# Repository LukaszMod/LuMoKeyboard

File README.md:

# LuMoKeyboard
Is is repository for LuMo keyboard in version 0.1

The splitted keyboard has 64 keys. I needed keyboard with all alphanum chars (36) + special chars(11) + duplicated functions keys like 2x space, 2x return, r/l alt, r/l ctrl r/l shift and rest. It is designed with Keith Choc keys to be as thin as possible. Communication is done by ProMicro controller using Bluetooth, so no cable is needed* . Additional feature is power sharing that allows to join and charge both parts in the same time and borrow powers from one part to the second one. Keyboard can work with 5 devices. Current configuration does not support display because of usage ProMicro instead of Nice!Nano.

\* For charging only

# Parts

List of components needed to build both halves of the keyboard.  
PCBs were ordered from **JLCPCB**, keyboard parts from **AliExpress**, and bolts/spacers from **TME.eu**.

---

## Component List

| Component                  | Quantity | Notes                                                    | Links
|----------------------------|----------|----------------------------------------------------------|-----------------------------------------------------
| PCB main                   | 2 files  | Gerber files in repository                               |
| PCB top                    | 2 files  | Gerber files in repository                               |
| PCB bottom                 | 2 files  | Gerber files in repository                               |
| Microcontroller            | 2        | Pro Micro NRF52840                                       | [link](https://pl.aliexpress.com/item/1005006271881076.html)
| On-Off switch              | 2        | SS12D10                                                  | [link](https://pl.aliexpress.com/item/1005005633418066.html)
| Tactile switch             | 2        | Push Button 6×6×4.3 mm DIP                               | [link](https://pl.aliexpress.com/item/1005005917191424.html)
| Diodes                     | 64       | 1N4148 (SMD SOD-123 used, standard is also possible)     | [link](https://pl.aliexpress.com/item/1005005707644429.html)
| Magnetic connector         | 1 set    | Magnetic Pogo Pin Connector 2 Positions MG02254B angled  | [link](https://pl.aliexpress.com/item/1005005687037973.html)
| Batteries                  | 2        | 301230 3.7V 120mAh with JST 1.25 connector + PCM         | [link](https://pl.aliexpress.com/item/4000174240984.html)
| Connectors                 | 2        | JST 1.25 2Pin Straight needle                            | [link](https://pl.aliexpress.com/item/1005009890700220.html)
| Sockets                    | 64       | Kailh Hot-Swappable PCB Socket for low profile switches  | [link](https://pl.aliexpress.com/item/1005003873653184.html)
| Switches                   | 64       | Kailh Low Profile Choc Switch V1 1350                    | [link](https://pl.aliexpress.com/item/1005008806799106.html)
| Keycaps                    | 64       | Low Profile Choc PBT Keycaps for Kailh 1350 Choc         | [link](https://pl.aliexpress.com/item/1005006734545486.html)
| Bolts                      | 4        | Screw M2×4; 0.4; cheese head; Phillips PH1               | [link](https://www.tme.eu/pl/details/m2x4_d7985/sruby/kraftberg/)
| Spacers                    | 4        | Screwed spacer sleeve; 5mm length; M2 thread; hexagonal  | [link](https://www.tme.eu/pl/en/details/tff-m2x5_dr111/metal-spacers/dremec/111x05/)
| Rubber feet                | 4        | 3mm thick                                                |
| Polymer clay plastic mass  | small bag| Borrowed from kids 😅                                    | [link](https://pl.aliexpress.com/item/1005010076052629.html)

---

## BOM Table (2025 Prices)

| Item                                      | Quantity | Price (USD)        |
|-------------------------------------------|----------|--------------------|
| PCBs (3 × 5, incl. duties/taxes/shipping) | –        | $57.85             |
| Pro Micro NRF52840                        | 2        | $3.84              |
| SS12D00 On-Off Mini Slide Switch 3pin     | 20       | $1.05              |
| Tactile Push Button Switches              | 50       | $1.41              |
| SMD SOD-123 diode 1N4148                  | 100      | $1.25              |
| Magnetic Pogo Pin Connector (2 pos.)      | 1 set    | $1.78              |
| 301030 3.7V 120mAh battery                | 2        | $4.54              |
| JST 1.25 connectors                       | 10       | $1.25              |
| Kailh Hot-Swappable PCB Socket            | 100      | $13.39             |
| Kailh Low Profile Choc Switch V1 1350     | 70       | $26.28             |
| Keycaps                                   | 70       | $41.89             |
| Screwed spacer                            | 10       | $3.90              |
| Bolts                                     | 100      | $1.80              |
| Rubber Feet                               | 100      | $1.66              |
| Polymer clay plastic mass                 | –        | ?? (borrowed)      |

**Total cost: $161.89 + guilt** 😅  

---

# Tools Needed

Tweezers, soldering iron, solder paste, solder wire, cutters, isopropyl alcohol, screwdriver.

---

# Soldering

The first components to solder are the diodes. Diodes can be SMD or through-hole. For through-hole diodes, solder from the same side as the component (bottom side). The top side of the PCB should remain flat, without any leads. For SMD diodes, this issue does not exist. Diodes must be soldered according to the orientation &#x1CC0F;. The vertical line is also marked on the diode itself. 

To solder SMD components, first apply a small amount of solder paste to one pad, then place a drop of molten solder on the pad. Hold the SMD component with tweezers, reheat the solder, and attach one lead. Once it solidifies, solder the second lead.

Next, solder the sockets on the main PCB. Before soldering, press the switches into the top plate. Then join the top and main PCBs, and press the sockets from below. These two plates will not be separated again. After soldering, check all connections with a multimeter.

The next components to solder are the microcontroller, switches, JST connectors, and magnetic connectors. Ensure there is enough space between the microcontroller and PCB for the battery. On my PCB, I used a different JST connector, so I had to secure it with hot glue.

Finally, assemble the plates. First, screw the bolts through the top and middle plates into the spacers. Then attach the bottom plate and fasten it with the remaining bolts. Press foam clay into the space between the PCB plates. To smooth the surface of the joint, use a wet finger.

# Flash

## Installation of zmk 

The installation are provide on the webside:

[Installation zmk](https://zmk.dev/docs/user-setup#prerequisites)

Do not execute next sestion- 'Config Repo Setup'. 
After that copy folder `lumo` located in `zmk` from current repository into
`zmk/app/boards/shields`. Next open startscript.sh and set path to python virtual environment (line source /path_to_venv/bin/activate). At the end execute the file. 

Connect the left part of keyboard by USB to PC. Click twice reset button on the keyboard - MCU will be set in boot mode and you shall see new mounted device. Copy file `zmk/app/build/lumo_left/zephyr/zmk.uf2` into the device. Do the same steps for right part.

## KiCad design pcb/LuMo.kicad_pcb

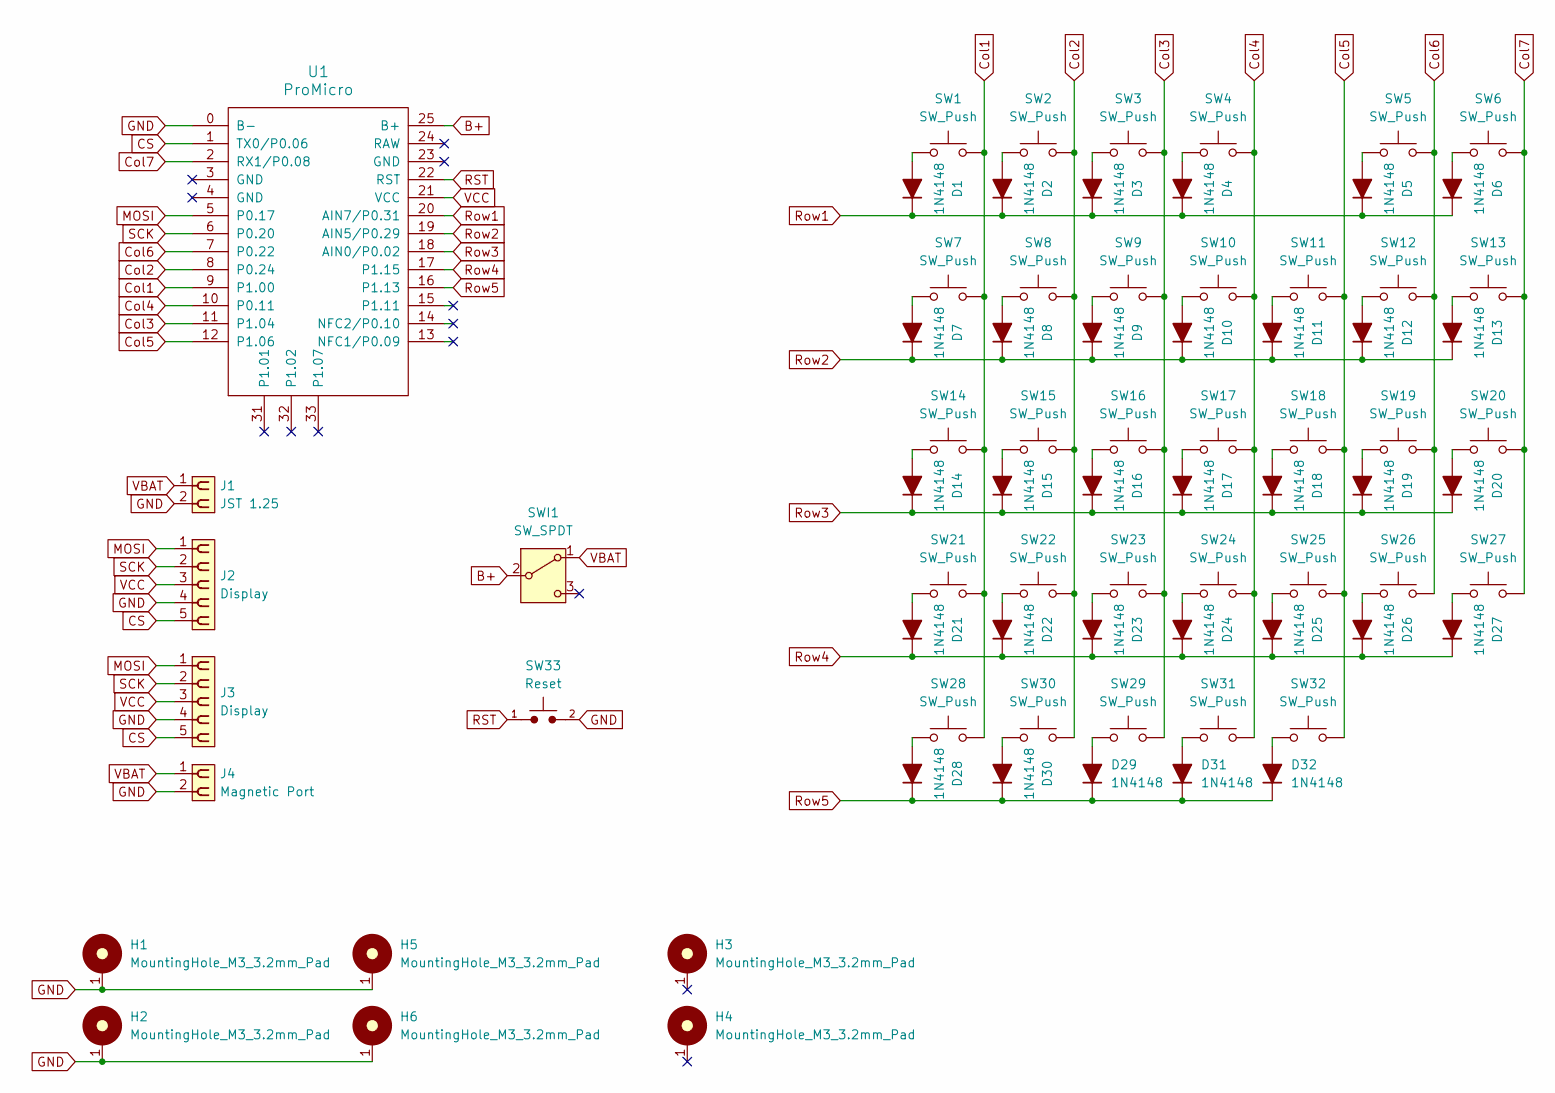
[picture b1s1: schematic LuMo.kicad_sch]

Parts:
D1, D2, D3, D4, D5, D6, D7, D8, D9, D10, D11, D12, D13, D14, D15, D16, D17, D18, D19, D20, D21, D22, D23, D24, D25, D26, D27, D28, D29, D30, D31, D32: 1N4148; crkbd-diode
H1, H2, H3, H4, H5, H6: MountingHole_M3_3.2mm_Pad; MountingHole_3.2mm_Pad
J1: JST 1.25; PinHeader_1x02_P1.27mm_Vertical
J2, J3: Display; PinSocket_1x05_P2.54mm_Vertical
J4: Magnetic Port; Magnetic connector
SW1, SW2, SW3, SW4, SW5, SW6, SW7, SW8, SW9, SW10, SW11, SW12, SW13, SW14, SW15, SW16, SW17, SW18, SW19, SW20, SW21, SW22, SW23, SW24, SW25, SW26, SW27, SW28, SW29, SW30, SW31, SW32: SW_Push; Kailh_socket_PG1350_reversible
SW33: Reset; SW_PUSH_6mm
SWI1: SW_SPDT; SW_Slide-03_-WS-SLTV_87x4x6.4_P2.54mm
U1: ProMicro; nice_nano

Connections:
B+: SWI1.2 (B), U1.25 (B+)
CS: J2.5, J3.5, U1.1 (TX0/P0.06)
Col1: SW1.2, SW7.2, SW14.2, SW21.2, SW28.2, U1.9 (P1.00)
Col2: SW2.2, SW8.2, SW15.2, SW22.2, SW30.2, U1.8 (P0.24)
Col3: SW3.2, SW9.2, SW16.2, SW23.2, SW29.2, U1.11 (P1.04)
Col4: SW4.2, SW10.2, SW17.2, SW24.2, SW31.2, U1.10 (P0.11)
Col5: SW11.2, SW18.2, SW25.2, SW32.2, U1.12 (P1.06)
Col6: SW5.2, SW12.2, SW19.2, SW26.2, U1.7 (P0.22)
Col7: SW6.2, SW13.2, SW20.2, SW27.2, U1.2 (RX1/P0.08)
GND: H1.1, H2.1, H5.1, H6.1, J1.2, J2.4, J3.4, J4.2, SW33.2, U1.0 (B-)
MOSI: J2.1, J3.1, U1.5 (P0.17)
unnamed: D1.2 (A), SW1.1
unnamed: D2.2 (A), SW2.1
unnamed: D3.2 (A), SW3.1
unnamed: D4.2 (A), SW4.1
unnamed: D5.2 (A), SW5.1
unnamed: D6.2 (A), SW6.1
unnamed: D7.2 (A), SW7.1
unnamed: D8.2 (A), SW8.1
unnamed: D9.2 (A), SW9.1
unnamed: D10.2 (A), SW10.1
unnamed: D11.2 (A), SW11.1
unnamed: D12.2 (A), SW12.1
unnamed: D13.2 (A), SW13.1
unnamed: D14.2 (A), SW14.1
unnamed: D15.2 (A), SW15.1
unnamed: D16.2 (A), SW16.1
unnamed: D17.2 (A), SW17.1
unnamed: D18.2 (A), SW18.1
unnamed: D19.2 (A), SW19.1
unnamed: D20.2 (A), SW20.1
unnamed: D21.2 (A), SW21.1
unnamed: D22.2 (A), SW22.1
unnamed: D23.2 (A), SW23.1
unnamed: D24.2 (A), SW24.1
unnamed: D25.2 (A), SW25.1
unnamed: D26.2 (A), SW26.1
unnamed: D27.2 (A), SW27.1
unnamed: D28.2 (A), SW28.1
unnamed: D29.2 (A), SW29.1
unnamed: D30.2 (A), SW30.1
unnamed: D31.2 (A), SW31.1
unnamed: D32.2 (A), SW32.1
RST: SW33.1, U1.22 (RST)
Row1: D1.1 (K), D2.1 (K), D3.1 (K), D4.1 (K), D5.1 (K), D6.1 (K), U1.20 (AIN7/P0.31)
Row2: D7.1 (K), D8.1 (K), D9.1 (K), D10.1 (K), D11.1 (K), D12.1 (K), D13.1 (K), U1.19 (AIN5/P0.29)
Row3: D14.1 (K), D15.1 (K), D16.1 (K), D17.1 (K), D18.1 (K), D19.1 (K), D20.1 (K), U1.18 (AIN0/P0.02)
Row4: D21.1 (K), D22.1 (K), D23.1 (K), D24.1 (K), D25.1 (K), D26.1 (K), D27.1 (K), U1.17 (P1.15)
Row5: D28.1 (K), D29.1 (K), D30.1 (K), D31.1 (K), D32.1 (K), U1.16 (P1.13)
SCK: J2.2, J3.2, U1.6 (P0.20)
VBAT: J1.1, J4.1, SWI1.1 (A)
VCC: J2.3, J3.3, U1.21 (VCC)

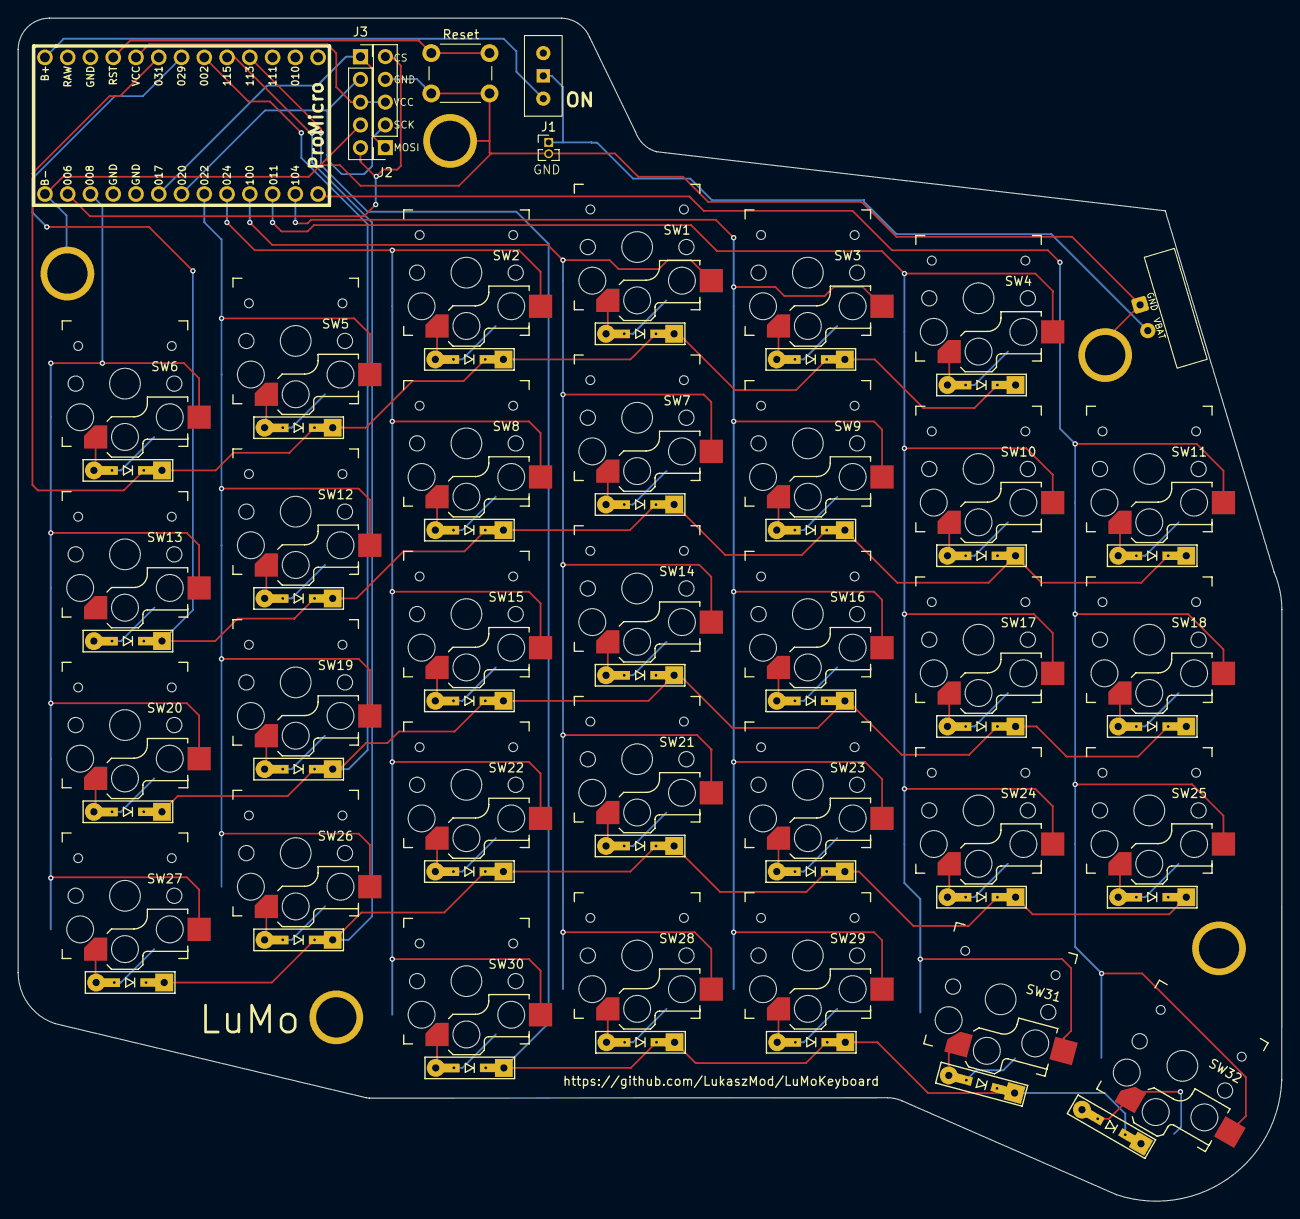
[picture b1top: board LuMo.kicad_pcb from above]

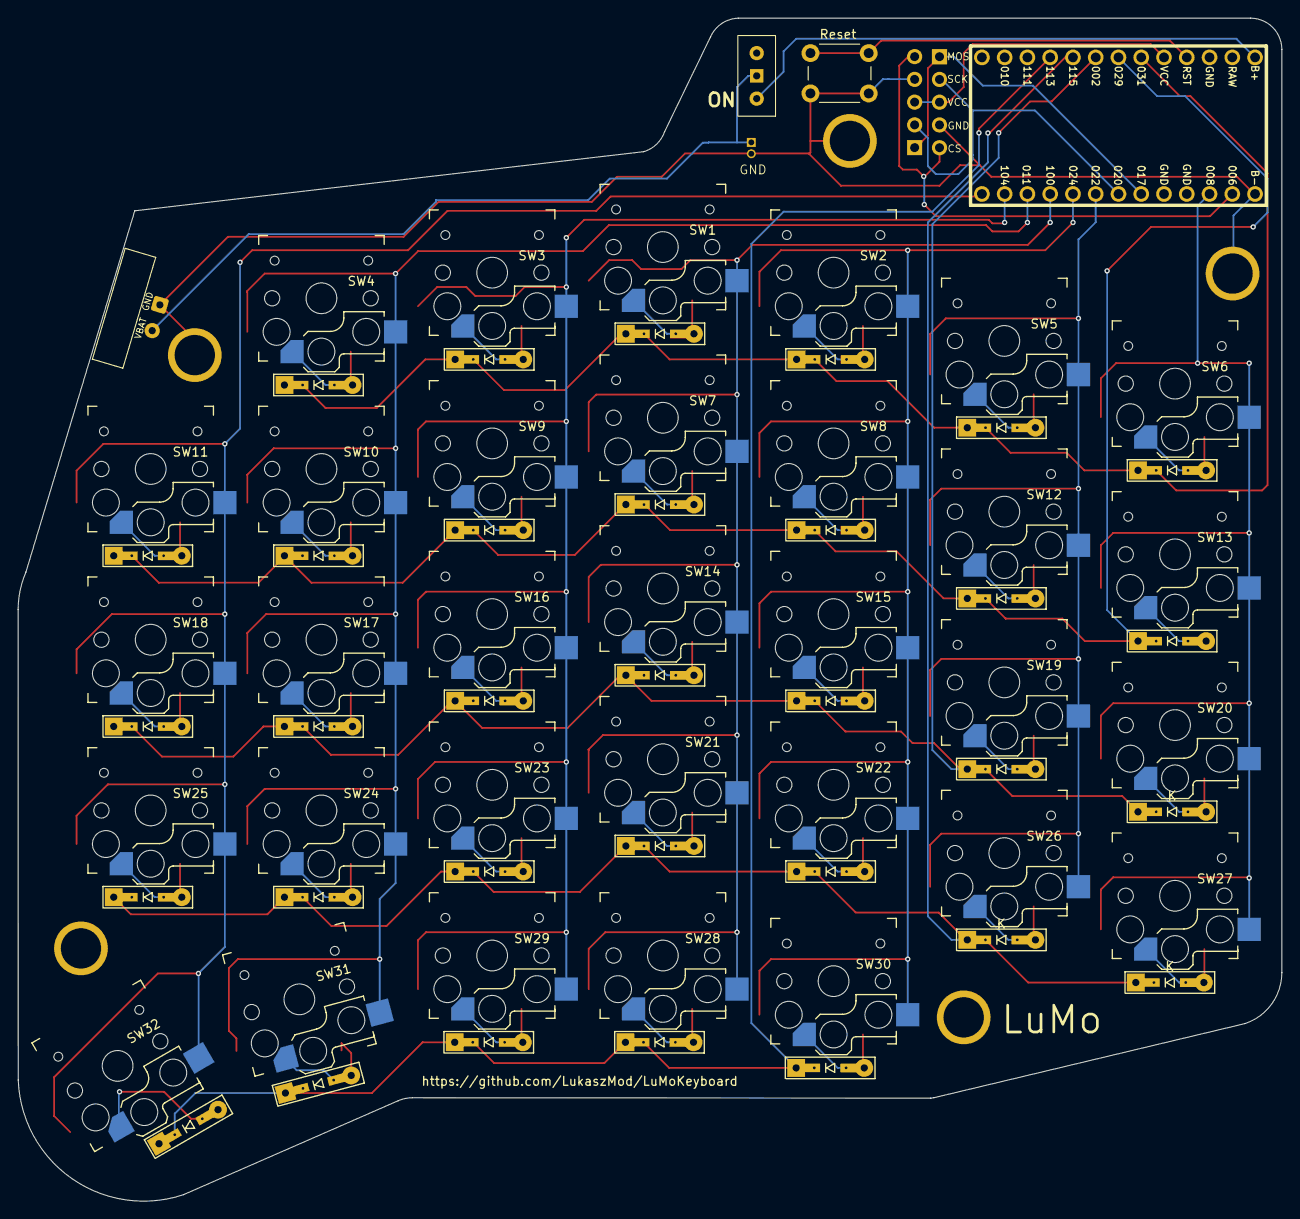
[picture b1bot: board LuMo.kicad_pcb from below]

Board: 2 copper layers, 141.0 x 132.0 mm, 76 parts (32 on the bottom side), 52 nets.

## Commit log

2025-08-17 Add draft version of PCB
2025-09-17 add first version of PCB
2025-11-17 update kicad project
2025-11-17 update gitignore
2025-11-17 add zmk
2025-12-31 update readme and update firmware files
